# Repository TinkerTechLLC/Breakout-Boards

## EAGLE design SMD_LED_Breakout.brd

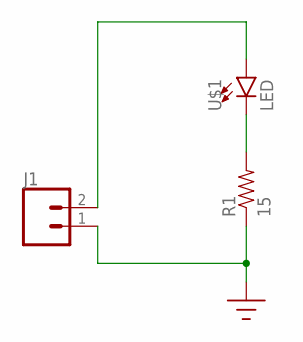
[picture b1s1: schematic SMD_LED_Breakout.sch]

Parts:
J1: CONN_02; 1X02
R1: 15; AXIAL-0.6
U$1: LED; VSMY7852X01-GS08

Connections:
GND: J1.1, R1.P$1 (1)
GND_PATH: R1.P$2 (2), U$1.- (C)
VIN: J1.2, U$1.+ (A)

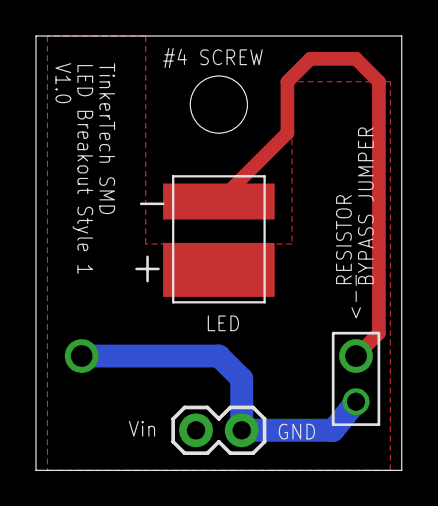
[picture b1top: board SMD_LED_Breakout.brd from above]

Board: 2 copper layers, 20.3 x 24.1 mm, 3 parts (1 on the bottom side), 3 nets.

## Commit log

2017-07-21 Initial commit
    Initial version sent for fab

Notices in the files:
parts and their libraries:
SparkFun-Connectors: Licensing: Creative Commons ShareAlike 4.0 International - https://creativecommons.org/licenses/by-sa/4.0
SparkFun-Passives: Licensing: CC v3.0 Share-Alike You are welcome to use this library for commercial purposes.
